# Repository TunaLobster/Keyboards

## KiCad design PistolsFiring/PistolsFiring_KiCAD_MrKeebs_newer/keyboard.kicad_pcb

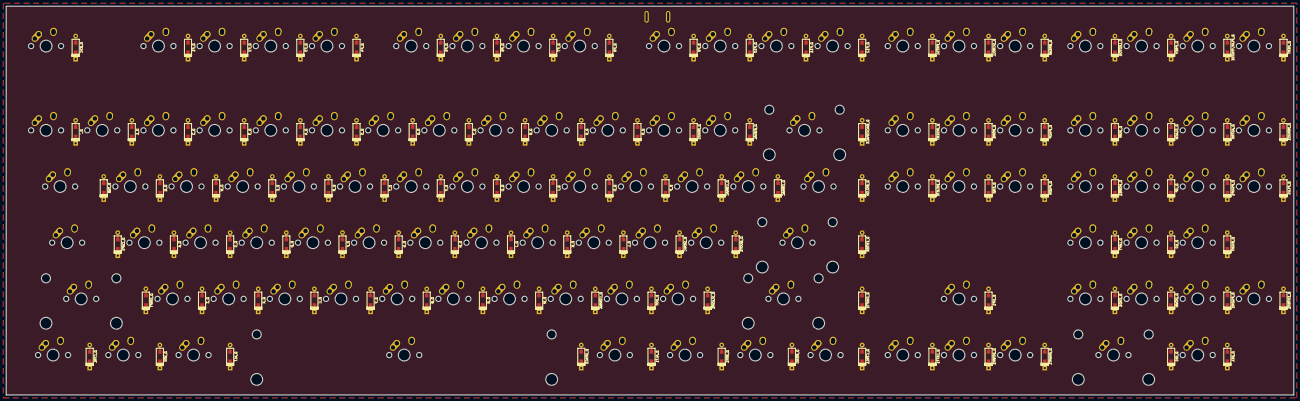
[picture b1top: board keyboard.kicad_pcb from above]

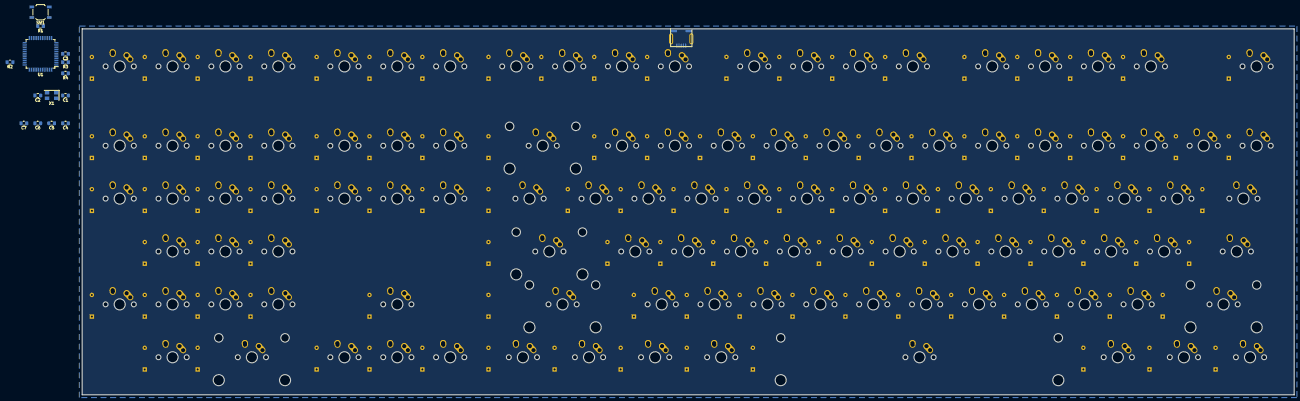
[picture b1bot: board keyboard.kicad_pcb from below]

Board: 2 copper layers, 436.6 x 131.8 mm, 231 parts (15 on the bottom side), 140 nets, no tracks yet.

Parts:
C1, C2, C3, C4, C5, C6, C7: 22pF; C_0805_2012Metric_Pad1.15x1.40mm_HandSolder
D_0, D_1, D_2, D_3, D_4, D_5, D_6, D_7, D_8, D_9, D_10: D; D_SOD123_axial
D_A: D; D_SOD123_axial
D_ALT, D_ALT1: D; D_SOD123_axial
D_ASTRK: D; D_SOD123_axial
D_B: D; D_SOD123_axial
D_BACKSPACE: D; D_SOD123_axial
D_BREAK: D; D_SOD123_axial
D_BSLSH: D; D_SOD123_axial
D_C: D; D_SOD123_axial
D_CAPS: D; D_SOD123_axial
D_CBRAC: D; D_SOD123_axial
D_COMMA: D; D_SOD123_axial
D_CTRL, D_CTRL1: D; D_SOD123_axial
D_D: D; D_SOD123_axial
D_DEL: D; D_SOD123_axial
D_DELETE: D; D_SOD123_axial
D_DOT: D; D_SOD123_axial
D_DOWN, D_DOWN1: D; D_SOD123_axial
D_E: D; D_SOD123_axial
D_END, D_END1: D; D_SOD123_axial
D_ENTER, D_ENTER1: D; D_SOD123_axial
D_EQUAL: D; D_SOD123_axial
D_ESC: D; D_SOD123_axial
D_F, D_F1, D_F2, D_F3, D_F4, D_F5, D_F6, D_F7, D_F8, D_F9, D_F10, D_F11, D_F12: D; D_SOD123_axial
D_G: D; D_SOD123_axial
D_H: D; D_SOD123_axial
D_HOME, D_HOME1: D; D_SOD123_axial
D_I: D; D_SOD123_axial
D_INS: D; D_SOD123_axial
D_INSERT: D; D_SOD123_axial
D_J: D; D_SOD123_axial
D_K: D; D_SOD123_axial
D_L: D; D_SOD123_axial
D_LEDTOG: D; D_SOD123_axial
D_LEFT, D_LEFT1: D; D_SOD123_axial
D_M: D; D_SOD123_axial
D_MENU: D; D_SOD123_axial
D_MINUS, D_MINUS1: D; D_SOD123_axial
D_N: D; D_SOD123_axial
D_NEXT: D; D_SOD123_axial
D_NUM: D; D_SOD123_axial
D_O: D; D_SOD123_axial
D_OBRAC: D; D_SOD123_axial
D_P: D; D_SOD123_axial
D_PGDN, D_PGDN1: D; D_SOD123_axial
D_PGUP, D_PGUP1: D; D_SOD123_axial
D_PLAY/PAUSE: D; D_SOD123_axial
D_PLUS: D; D_SOD123_axial
D_PREV: D; D_SOD123_axial
D_PRTSC: D; D_SOD123_axial
D_Q: D; D_SOD123_axial
D_QUOTE: D; D_SOD123_axial
D_R: D; D_SOD123_axial
D_RIGHT, D_RIGHT1: D; D_SOD123_axial
D_S: D; D_SOD123_axial
D_SCROLL: D; D_SOD123_axial
D_SEMIC: D; D_SOD123_axial
D_SHIFT, D_SHIFT1: D; D_SOD123_axial
D_SLASH, D_SLASH1: D; D_SOD123_axial
D_SPACE: D; D_SOD123_axial
D_T: D; D_SOD123_axial
D_TAB: D; D_SOD123_axial
D_U: D; D_SOD123_axial
D_UP, D_UP1: D; D_SOD123_axial
D_V: D; D_SOD123_axial
D_W: D; D_SOD123_axial
D_WIN, D_WIN1: D; D_SOD123_axial
D_X: D; D_SOD123_axial
D_Y: D; D_SOD123_axial
D_Z: D; D_SOD123_axial
D_`: D; D_SOD123_axial
K_0, K_1, K_2, K_3, K_4, K_5, K_6, K_7, K_8, K_9, K_10: KEYSW; MX-1U-NoLED
K_A: KEYSW; MX-1U-NoLED
K_ALT, K_ALT1: KEYSW; MX-1.25U-NoLED
K_ASTRK: KEYSW; MX-1U-NoLED
K_B: KEYSW; MX-1U-NoLED
K_BACKSPACE: KEYSW; MX-2U-NoLED
K_BREAK: KEYSW; MX-1U-NoLED
K_BSLSH: KEYSW; MX-1.5U-NoLED
K_C: KEYSW; MX-1U-NoLED
K_CAPS: KEYSW; MX-1.75U-NoLED
K_CBRAC: KEYSW; MX-1U-NoLED
K_COMMA: KEYSW; MX-1U-NoLED
K_CTRL, K_CTRL1: KEYSW; MX-1.25U-NoLED
K_D: KEYSW; MX-1U-NoLED
K_DEL: KEYSW; MX-1U-NoLED
K_DELETE: KEYSW; MX-1U-NoLED
K_DOT: KEYSW; MX-1U-NoLED
K_DOWN, K_DOWN1: KEYSW; MX-1U-NoLED
K_E: KEYSW; MX-1U-NoLED
K_END, K_END1: KEYSW; MX-1U-NoLED
K_ENTER: KEYSW; MX-2.25U-NoLED
K_ENTER1: KEYSW; MX-1U-NoLED
K_EQUAL: KEYSW; MX-1U-NoLED
K_ESC: KEYSW; MX-1U-NoLED
K_F, K_F1, K_F2, K_F3, K_F4, K_F5, K_F6, K_F7, K_F8, K_F9, K_F10, K_F11, K_F12: KEYSW; MX-1U-NoLED
K_G: KEYSW; MX-1U-NoLED
K_H: KEYSW; MX-1U-NoLED
K_HOME, K_HOME1: KEYSW; MX-1U-NoLED
K_I: KEYSW; MX-1U-NoLED
K_INS: KEYSW; MX-2U-NoLED
K_INSERT: KEYSW; MX-1U-NoLED
K_J: KEYSW; MX-1U-NoLED
K_K: KEYSW; MX-1U-NoLED
K_L: KEYSW; MX-1U-NoLED
K_LEDTOG: KEYSW; MX-1U-NoLED
K_LEFT, K_LEFT1: KEYSW; MX-1U-NoLED
K_M: KEYSW; MX-1U-NoLED
K_MENU: KEYSW; MX-1.25U-NoLED
K_MINUS, K_MINUS1: KEYSW; MX-1U-NoLED
K_N: KEYSW; MX-1U-NoLED
K_NEXT: KEYSW; MX-1U-NoLED
K_NUM: KEYSW; MX-1U-NoLED
K_O: KEYSW; MX-1U-NoLED
K_OBRAC: KEYSW; MX-1U-NoLED
K_P: KEYSW; MX-1U-NoLED
K_PGDN, K_PGDN1: KEYSW; MX-1U-NoLED
K_PGUP, K_PGUP1: KEYSW; MX-1U-NoLED
K_PLAY/PAUSE: KEYSW; MX-1U-NoLED
K_PLUS: KEYSW; MX-1U-NoLED
K_PREV: KEYSW; MX-1U-NoLED
K_PRTSC: KEYSW; MX-1U-NoLED
K_Q: KEYSW; MX-1U-NoLED
K_QUOTE: KEYSW; MX-1U-NoLED
K_R: KEYSW; MX-1U-NoLED
K_RIGHT, K_RIGHT1: KEYSW; MX-1U-NoLED
K_S: KEYSW; MX-1U-NoLED
K_SCROLL: KEYSW; MX-1U-NoLED
K_SEMIC: KEYSW; MX-1U-NoLED
K_SHIFT: KEYSW; MX-2.25U-NoLED
K_SHIFT1: KEYSW; MX-2.75U-NoLED
K_SLASH, K_SLASH1: KEYSW; MX-1U-NoLED
K_SPACE: KEYSW; MX-6.25U-NoLED
K_T: KEYSW; MX-1U-NoLED
K_TAB: KEYSW; MX-1.5U-NoLED
K_U: KEYSW; MX-1U-NoLED
K_UP, K_UP1: KEYSW; MX-1U-NoLED
K_V: KEYSW; MX-1U-NoLED
K_W: KEYSW; MX-1U-NoLED
K_WIN, K_WIN1: KEYSW; MX-1.25U-NoLED
K_X: KEYSW; MX-1U-NoLED
K_Y: KEYSW; MX-1U-NoLED
K_Z: KEYSW; MX-1U-NoLED
K_`: KEYSW; MX-1U-NoLED
R1, R2: 10k; R_0805_2012Metric_Pad1.15x1.40mm_HandSolder
R3, R4: 22u; R_0805_2012Metric_Pad1.15x1.40mm_HandSolder
SW1: SW_PUSH; SW_SPST_TL3342
U1: ATMEGA32U4; TQFP-44_10x10mm_P0.8mm
USB1: USB_mini_micro_B; USB_miniB_hirose_5S8
X1: XTAL_GND; Crystal_SMD_5032-4Pin_5.0x3.2mm

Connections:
/col0: D_CAPS.1, D_CTRL.1, D_ESC.1, D_TAB.1, D_`.1, K_CAPS.1, K_CTRL.1, K_ESC.1, K_TAB.1, K_`.1
/col1: D_1.1, D_SHIFT.1, D_WIN.1, K_1.1, K_SHIFT.1, K_WIN.1, U1.31
/col2: D_2.1, D_A.1, D_F1.1, D_Q.1, D_Z.1, K_2.1, K_A.1, K_F1.1, K_Q.1, K_Z.1, U1.32
/col3: D_3.1, D_ALT.1, D_F2.1, D_S.1, D_W.1, D_X.1, K_3.1, K_ALT.1, K_F2.1, K_S.1, K_W.1, K_X.1, U1.18
/col4: D_4.1, D_C.1, D_D.1, D_E.1, D_F3.1, K_4.1, K_C.1, K_D.1, K_E.1, K_F3.1, U1.19
/col5: D_5.1, D_F.1, D_F4.1, D_R.1, D_V.1, K_5.1, K_F.1, K_F4.1, K_R.1, K_V.1, U1.20
/col6: D_6.1, D_B.1, D_G.1, D_SPACE.1, D_T.1, K_6.1, K_B.1, K_G.1, K_SPACE.1, K_T.1, U1.21
/col7: D_7.1, D_F5.1, D_H.1, D_N.1, D_Y.1, K_7.1, K_F5.1, K_H.1, K_N.1, K_Y.1, U1.25
/col8: D_8.1, D_F6.1, D_J.1, D_M.1, D_U.1, K_8.1, K_F6.1, K_J.1, K_M.1, K_U.1, U1.22
/col9: D_9.1, D_COMMA.1, D_F7.1, D_I.1, D_K.1, K_9.1, K_COMMA.1, K_F7.1, K_I.1, K_K.1, U1.26
/col10: D_0.1, D_ALT1.1, D_DOT.1, D_F8.1, D_L.1, D_O.1, K_0.1, K_ALT1.1, K_DOT.1, K_F8.1, K_L.1, K_O.1, U1.27
/col11: D_F9.1, D_MINUS.1, D_P.1, D_SEMIC.1, D_SLASH1.1, D_WIN1.1, K_F9.1, K_MINUS.1, K_P.1, K_SEMIC.1, K_SLASH1.1, K_WIN1.1
/col12: D_CBRAC.1, D_EQUAL.1, D_F10.1, D_QUOTE.1, K_CBRAC.1, K_EQUAL.1, K_F10.1, K_QUOTE.1
/col13: D_ENTER.1, D_F11.1, D_MENU.1, D_OBRAC.1, D_SHIFT1.1, K_ENTER.1, K_F11.1, K_MENU.1, K_OBRAC.1, K_SHIFT1.1, U1.33
/col14: D_BACKSPACE.1, D_BSLSH.1, D_CTRL1.1, D_F12.1, K_BACKSPACE.1, K_BSLSH.1, K_CTRL1.1, K_F12.1
/col15: D_DELETE.1, D_INSERT.1, D_LEFT1.1, D_PRTSC.1, K_DELETE.1, K_INSERT.1, K_LEFT1.1, K_PRTSC.1
/col16: D_DOWN1.1, D_END.1, D_HOME.1, D_SCROLL.1, D_UP1.1, K_DOWN1.1, K_END.1, K_HOME.1, K_SCROLL.1, K_UP1.1
/col17: D_BREAK.1, D_PGDN.1, D_PGUP.1, D_RIGHT1.1, K_BREAK.1, K_PGDN.1, K_PGUP.1, K_RIGHT1.1
/col19: D_END1.1, D_HOME1.1, D_INS.1, D_LEDTOG.1, D_LEFT.1, D_NUM.1, K_END1.1, K_HOME1.1, K_INS.1, K_LEDTOG.1, K_LEFT.1, K_NUM.1, U1.41
/col20: D_10.1, D_DOWN.1, D_PREV.1, D_SLASH.1, D_UP.1, K_10.1, K_DOWN.1, K_PREV.1, K_SLASH.1, K_UP.1, U1.40
/col21: D_ASTRK.1, D_DEL.1, D_PGDN1.1, D_PGUP1.1, D_PLAY/PAUSE.1, D_RIGHT.1, K_ASTRK.1, K_DEL.1, K_PGDN1.1, K_PGUP1.1, K_PLAY/PAUSE.1, K_RIGHT.1
/col22: D_ENTER1.1, D_MINUS1.1, D_NEXT.1, D_PLUS.1, K_ENTER1.1, K_MINUS1.1, K_NEXT.1, K_PLUS.1
GND: C1.2, C2.2, C3.2, C4.2, C5.2, C6.2, C7.2, R2.2, SW1.1, U1.5, U1.15, U1.23, USB1.5, USB1.6, X1.3
unnamed: C1.1, U1.16, X1.1
unnamed: C2.1, U1.17, X1.2
unnamed: C3.1, U1.6
unnamed: D_0.2, K_0.2
unnamed: D_1.2, K_1.2
unnamed: D_2.2, K_2.2
unnamed: D_3.2, K_3.2
unnamed: D_4.2, K_4.2
unnamed: D_5.2, K_5.2
unnamed: D_6.2, K_6.2
unnamed: D_7.2, K_7.2
unnamed: D_8.2, K_8.2
unnamed: D_9.2, K_9.2
unnamed: D_10.2, K_10.2
unnamed: D_A.2, K_A.2
unnamed: D_ALT1.2, K_ALT1.2
unnamed: D_ALT.2, K_ALT.2
unnamed: D_ASTRK.2, K_ASTRK.2
unnamed: D_B.2, K_B.2
unnamed: D_BACKSPACE.2, K_BACKSPACE.2
unnamed: D_BREAK.2, K_BREAK.2
unnamed: D_BSLSH.2, K_BSLSH.2
unnamed: D_C.2, K_C.2
unnamed: D_CAPS.2, K_CAPS.2
unnamed: D_CBRAC.2, K_CBRAC.2
unnamed: D_COMMA.2, K_COMMA.2
unnamed: D_CTRL1.2, K_CTRL1.2
unnamed: D_CTRL.2, K_CTRL.2
unnamed: D_D.2, K_D.2
unnamed: D_DEL.2, K_DEL.2
unnamed: D_DELETE.2, K_DELETE.2
unnamed: D_DOT.2, K_DOT.2
unnamed: D_DOWN1.2, K_DOWN1.2
unnamed: D_DOWN.2, K_DOWN.2
unnamed: D_E.2, K_E.2
unnamed: D_END1.2, K_END1.2
unnamed: D_END.2, K_END.2
unnamed: D_ENTER1.2, K_ENTER1.2
unnamed: D_ENTER.2, K_ENTER.2
unnamed: D_EQUAL.2, K_EQUAL.2
unnamed: D_ESC.2, K_ESC.2
unnamed: D_F1.2, K_F1.2
unnamed: D_F2.2, K_F2.2
unnamed: D_F3.2, K_F3.2
unnamed: D_F4.2, K_F4.2
unnamed: D_F5.2, K_F5.2
unnamed: D_F6.2, K_F6.2
unnamed: D_F7.2, K_F7.2
unnamed: D_F8.2, K_F8.2
unnamed: D_F9.2, K_F9.2
unnamed: D_F10.2, K_F10.2
unnamed: D_F11.2, K_F11.2
unnamed: D_F12.2, K_F12.2
unnamed: D_F.2, K_F.2
unnamed: D_G.2, K_G.2
unnamed: D_H.2, K_H.2
unnamed: D_HOME1.2, K_HOME1.2
unnamed: D_HOME.2, K_HOME.2
unnamed: D_I.2, K_I.2
unnamed: D_INS.2, K_INS.2
unnamed: D_INSERT.2, K_INSERT.2
unnamed: D_J.2, K_J.2
unnamed: D_K.2, K_K.2
unnamed: D_L.2, K_L.2
unnamed: D_LEDTOG.2, K_LEDTOG.2
unnamed: D_LEFT1.2, K_LEFT1.2
unnamed: D_LEFT.2, K_LEFT.2
unnamed: D_M.2, K_M.2
unnamed: D_MENU.2, K_MENU.2
unnamed: D_MINUS1.2, K_MINUS1.2
unnamed: D_MINUS.2, K_MINUS.2
unnamed: D_N.2, K_N.2
unnamed: D_NEXT.2, K_NEXT.2
unnamed: D_NUM.2, K_NUM.2
unnamed: D_O.2, K_O.2
unnamed: D_OBRAC.2, K_OBRAC.2
unnamed: D_P.2, K_P.2
unnamed: D_PGDN1.2, K_PGDN1.2
unnamed: D_PGDN.2, K_PGDN.2
unnamed: D_PGUP1.2, K_PGUP1.2
unnamed: D_PGUP.2, K_PGUP.2
unnamed: D_PLAY/PAUSE.2, K_PLAY/PAUSE.2
unnamed: D_PLUS.2, K_PLUS.2
unnamed: D_PREV.2, K_PREV.2
unnamed: D_PRTSC.2, K_PRTSC.2
unnamed: D_Q.2, K_Q.2
unnamed: D_QUOTE.2, K_QUOTE.2
unnamed: D_R.2, K_R.2
unnamed: D_RIGHT1.2, K_RIGHT1.2
unnamed: D_RIGHT.2, K_RIGHT.2
unnamed: D_S.2, K_S.2
unnamed: D_SCROLL.2, K_SCROLL.2
unnamed: D_SEMIC.2, K_SEMIC.2
unnamed: D_SHIFT1.2, K_SHIFT1.2
unnamed: D_SHIFT.2, K_SHIFT.2
unnamed: D_SLASH1.2, K_SLASH1.2
unnamed: D_SLASH.2, K_SLASH.2
unnamed: D_SPACE.2, K_SPACE.2
unnamed: D_T.2, K_T.2
unnamed: D_TAB.2, K_TAB.2
unnamed: D_U.2, K_U.2
unnamed: D_UP1.2, K_UP1.2
unnamed: D_UP.2, K_UP.2
unnamed: D_V.2, K_V.2
unnamed: D_W.2, K_W.2
unnamed: D_WIN1.2, K_WIN1.2
unnamed: D_WIN.2, K_WIN.2
unnamed: D_X.2, K_X.2
unnamed: D_Y.2, K_Y.2
unnamed: D_Z.2, K_Z.2
unnamed: D_`.2, K_`.2
unnamed: R1.1, SW1.2, U1.13
unnamed: R3.1, U1.3
unnamed: R4.1, U1.4
unnamed: R3.2, USB1.2
unnamed: R4.2, USB1.3
VCC: C4.1, C5.1, C6.1, C7.1, R1.2, U1.2, U1.14, U1.24, USB1.1

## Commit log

2019-09-29 PistolsFiring Update
    Quick idea from scratch. Probably won't be updated beyond this state for a while.
